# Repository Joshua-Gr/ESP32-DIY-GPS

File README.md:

# ESP32 DIY GPS

A GPS receiver board built around an ESP32-S3 and a u-blox GNSS module, powered from a 12 V vehicle supply.

## Repository layout

| Path | Contents |
|---|---|
| `firmware/` | PlatformIO project (Arduino framework) |
| `hardware/` | KiCad 10 project |
| `hardware/lib/` | Project-local symbols, footprints and 3D models, so the project opens without extra libraries installed |
| `hardware/fab/` | Fabrication outputs, one folder per ordered board revision |

## Hardware

80 × 40 mm, 4-layer PCB.

| Function | Part |
|---|---|
| MCU | Espressif ESP32-S3-WROOM-1-N16R2 (rated −40 to 85 °C ambient) |
| GNSS | u-blox NEO-M9N, external active antenna via U.FL (antenna bias from the receiver's VCC_RF) |
| Power | TI TPS54360 buck regulator, designed for 6–60 V in, 3.3 V / 1.5 A out |
| Input protection | Series Schottky (reverse polarity) and a 33 V TVS on the 12 V input |
| Connectors | 12 V input (Molex Micro-Fit 3.0), USB-C (data only, not powered), 3-pin debug UART header |

The schematic is split into sheets, each laid out in numbered blocks with design and layout notes:

| Sheet | Contents |
|---|---|
| Top level | Block diagram of how the sheets connect |
| Power | Input protection and the 3.3 V buck regulator |
| MCU | ESP32-S3 module, reset and boot buttons, decoupling, I/O series resistors |
| GNSS | NEO-M9N receiver, antenna feed, host UART and test points |
| Connectors | USB-C and the debug UART header |

## Firmware

The ESP32 bridges the GNSS receiver to USB and Bluetooth LE. At boot it sets the
NEO-M9N to 115200 baud and 10 Hz NMEA output (GGA, RMC, VTG, GSA every fix, GSV once
per second); after that every byte from the receiver is forwarded unchanged.

| Interface | Direction | Use |
|---|---|---|
| USB-C (CDC serial) | both | NMEA stream, gpsd, u-center (UBX passes through) |
| BLE Nordic UART Service, advertised as `ESP32-DIY-GPS-XXXX` | TX notify / RX write | NMEA to BLE GNSS apps, UBX commands back to the receiver |
| Debug header (UART0, 115200) | out | Boot and status log |

The board must be powered from the 12 V input; USB-C carries data only. Change the
rate with `-DNAV_RATE_HZ=<n>` in `build_flags`; above 10 Hz, reduce the NMEA sentence
set or switch to UBX output to stay within the serial bandwidth.

```sh
cd firmware
pio run            # build
pio run -t upload  # flash
```

## License

Firmware: GPL-3.0-or-later. Hardware design: CERN-OHL-S-2.0. Third-party
part library: CC-BY-SA-4.0. See [LICENSE.md](LICENSE.md).

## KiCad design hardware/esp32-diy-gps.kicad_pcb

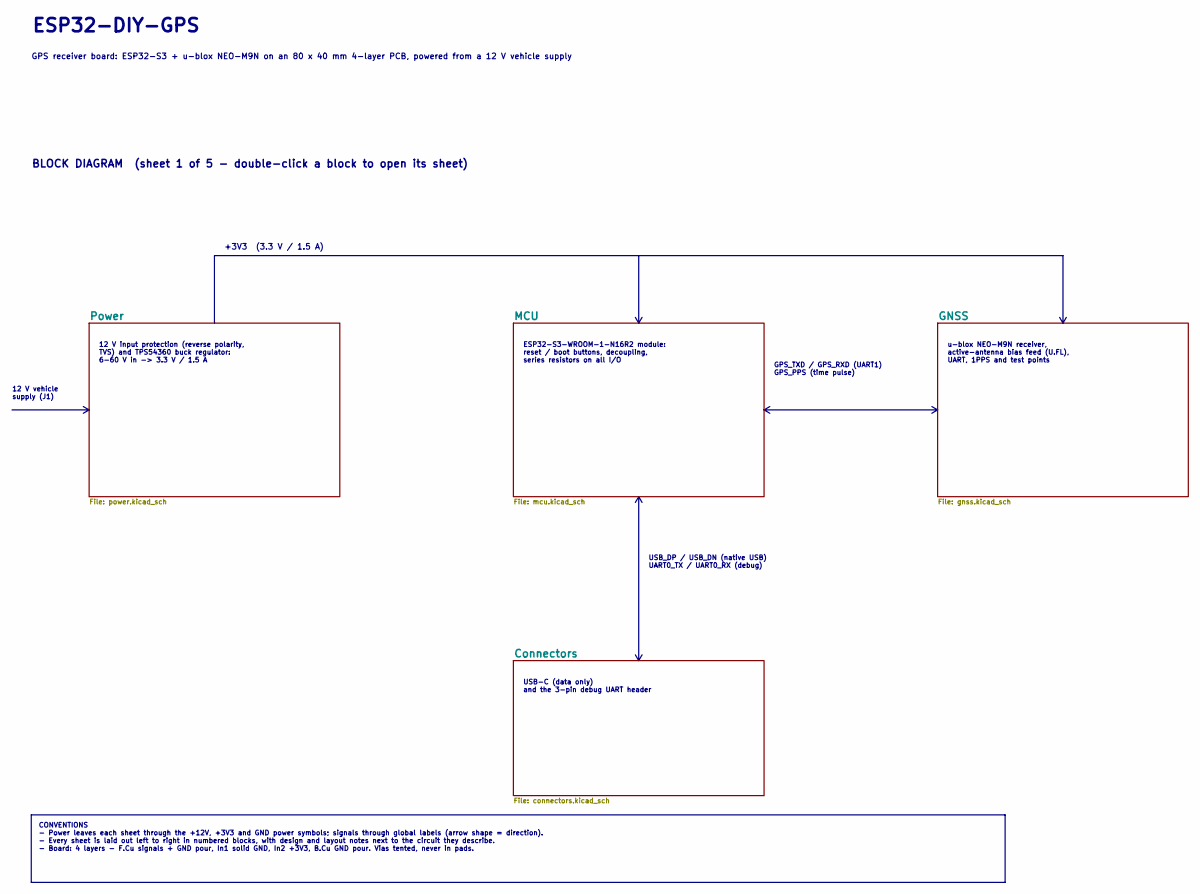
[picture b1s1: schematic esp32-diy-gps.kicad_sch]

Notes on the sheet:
ESP32-DIY-GPS
GPS receiver board: ESP32-S3 + u-blox NEO-M9N on an 80 x 40 mm 4-layer PCB, powered from a 12 V vehicle supply
BLOCK DIAGRAM (sheet 1 of 5 - double-click a block to open its sheet)
12 V input protection (reverse polarity, TVS) and TPS54360 buck regulator: 6-60 V in -> 3.3 V / 1.5 A
ESP32-S3-WROOM-1-N16R2 module: reset / boot buttons, decoupling, series resistors on all I/O
u-blox NEO-M9N receiver, active-antenna bias feed (U.FL), UART, 1PPS and test points
USB-C (data only) and the 3-pin debug UART header
12 V vehicle supply (J1)
+3V3 (3.3 V / 1.5 A)
GPS_TXD / GPS_RXD (UART1) GPS_PPS (time pulse)
USB_DP / USB_DN (native USB) UART0_TX / UART0_RX (debug)
CONVENTIONS - Power leaves each sheet through the +12V, +3V3 and GND power symbols; signals through global labels (arrow shape = direction). - Every sheet is laid out left to right in numbered blocks, with design and layout notes next to the circuit they describe. - Board: 4 layers - F.Cu signals +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

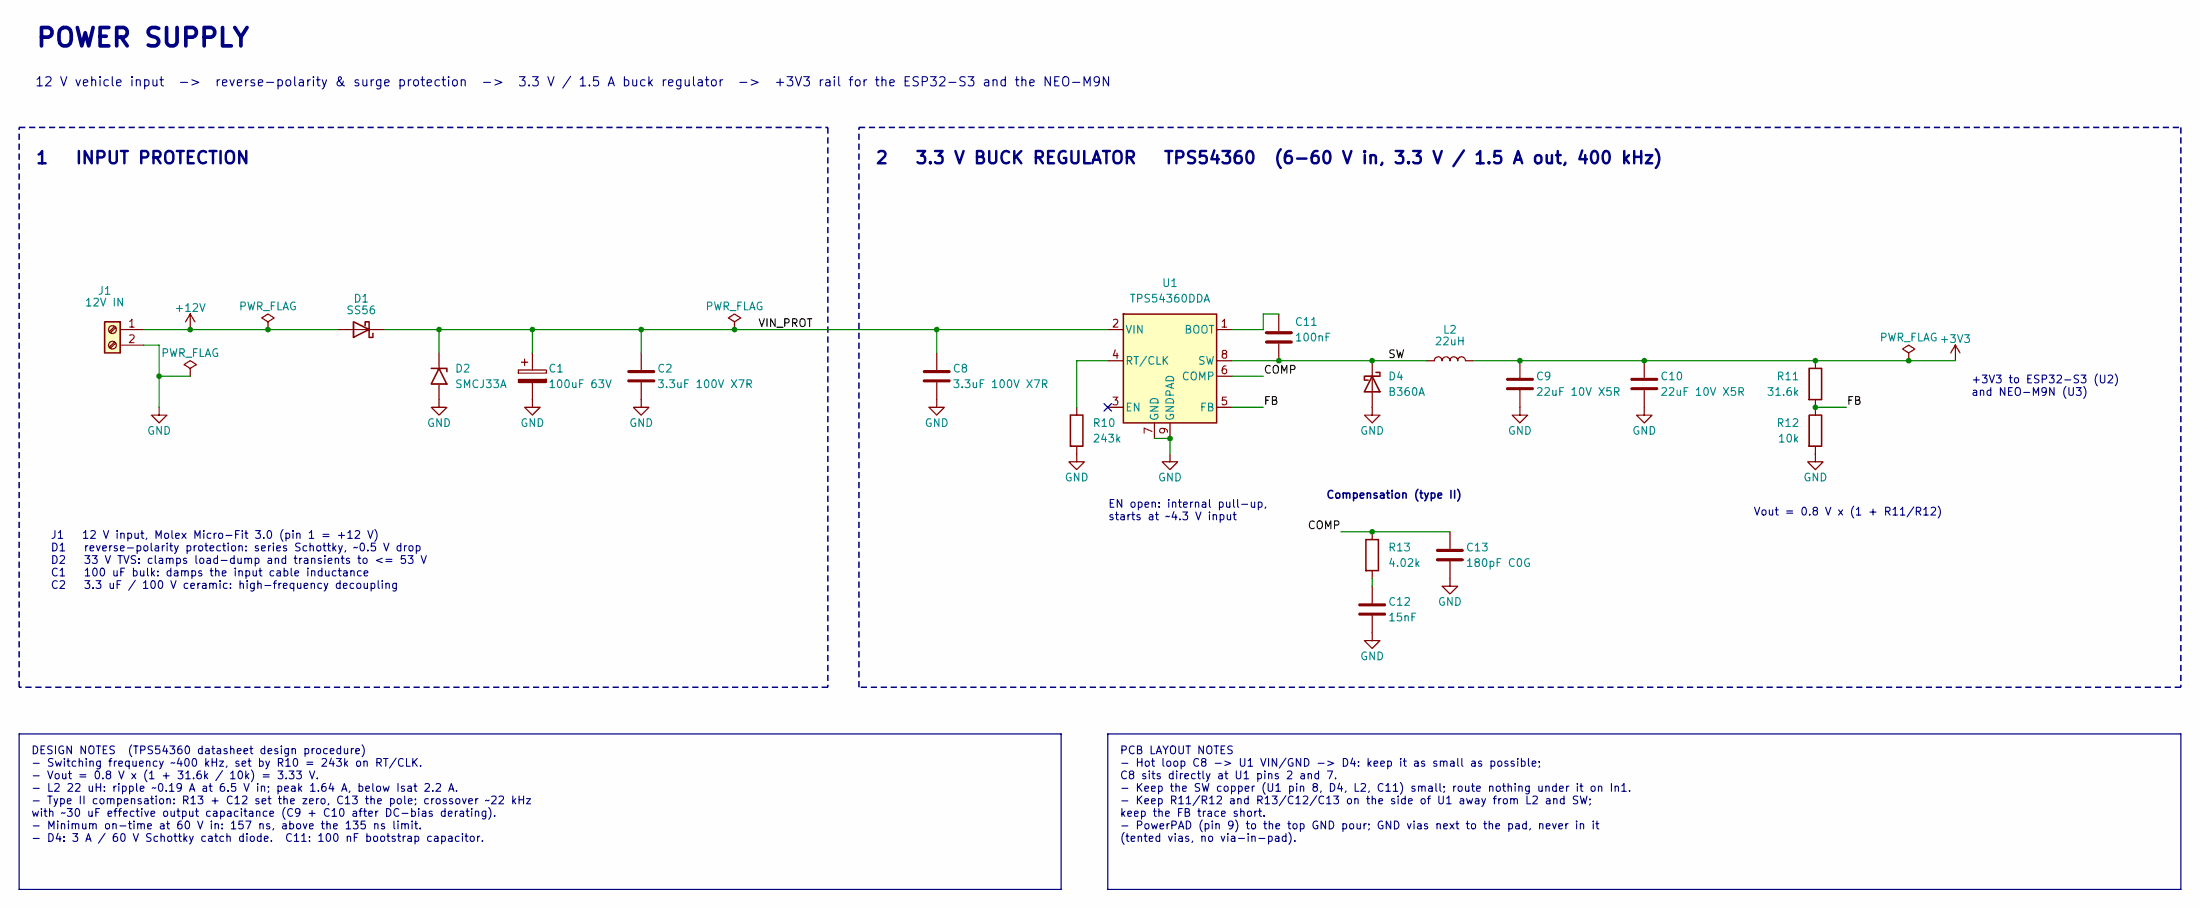
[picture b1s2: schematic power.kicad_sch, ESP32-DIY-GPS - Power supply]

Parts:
C1: 100uF 63V; CP_Elec_10x10; MPN EEE-FK1J101P
C2, C8: 3.3uF 100V X7R; C_1210_3225Metric; MPN FS32X335K101EGG
C9, C10: 22uF 10V X5R; C_0805_2012Metric; MPN CL21A226MPQNNNE
C11: 100nF; C_0805_2012Metric; MPN CL21B104KBCNNNC
C12: 15nF; C_0805_2012Metric; MPN CC0805KRX7R9BB153
C13: 180pF C0G; C_0805_2012Metric; MPN CC0805JRNPO9BN181
D1: SS56; D_SMC; MPN B560C-13-F
D2: SMCJ33A; D_SMC; MPN SMCJ33A
D4: B360A; D_SMA; MPN B360A-13-F
J1: 12V IN; Molex_Micro-Fit_3.0_43650-0212_1x02-1MP_P3.00mm_Horizontal; MPN 43650-0212
L2: 22uH; L_Sunlord_SWPA6045S; MPN SWPA6045S220MT
R10: 243k; R_0805_2012Metric; MPN 0805W8F2433T5E
R11: 31.6k; R_0805_2012Metric; MPN RC0805FR-0731K6L
R12: 10k; R_0805_2012Metric; MPN RC0805FR-0710KL
R13: 4.02k; R_0805_2012Metric; MPN RC0805FR-074K02L
U1: TPS54360DDA; TI_SO-PowerPAD-8; MPN TPS54360DDAR

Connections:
+3V3: C9.1, C10.1, L2.2, R11.1; also elsewhere on the board
+12V: D1.2 (A), J1.1
/Power/COMP: C13.1, R13.1, U1.6 (COMP)
/Power/FB: R11.2, R12.1, U1.5 (FB)
/Power/SW: C11.2, D4.1 (K), L2.1, U1.8 (SW)
/Power/VIN_PROT: C1.1, C2.1, C8.1, D1.1 (K), D2.1 (A1), U1.2 (VIN)
GND: C1.2, C2.2, C8.2, C9.2, C10.2, C12.2, C13.2, D2.2 (A2), D4.2 (A), J1.2, R10.2, R12.2, U1.7 (GND), U1.9 (GNDPAD); also elsewhere on the board
unnamed: C12.1, R13.2
unnamed: C11.1, U1.1 (BOOT)
unnamed: R10.1, U1.4 (RT/CLK)

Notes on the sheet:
EN open: internal pull-up, starts at ~4.3 V input
Compensation (type II)
12 V vehicle input -> reverse-polarity & surge protection -> 3.3 V / 1.5 A buck regulator -> +3V3 rail for the ESP32-S3 and the NEO-M9N
2 3.3 V BUCK REGULATOR TPS54360 (6-60 V in, 3.3 V / 1.5 A out, 400 kHz)
1 INPUT PROTECTION
J1 12 V input, Molex Micro-Fit 3.0 (pin 1 = +12 V) D1 reverse-polarity protection: series Schottky, ~0.5 V drop D2 33 V TVS: clamps load-dump and transients to <= 53 V C1 100 uF bulk: damps the input cable inductance C2 3.3 uF / 100 V ceramic: high-frequency decoupling
+3V3 to ESP32-S3 (U2) and NEO-M9N (U3)
POWER SUPPLY
Vout = 0.8 V x (1 + R11/R12)
PCB LAYOUT NOTES - Hot loop C8 -> U1 VIN/GND -> D4: keep it as small as possible; C8 sits directly at U1 pins 2 and 7. - Keep the SW copper (U1 pin 8, D4, L2, C11) small; route nothing under it on In1. - Keep R11/R12 and R13/C12/C13 on the side of U1 away from L2 and SW; keep the FB trace short. - 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
DESIGN NOTES (TPS54360 datasheet design procedure) - Switching frequency ~400 kHz, set by R10 = 243k on RT/CLK. - Vout = 0.8 V x (1 + 31.6k / 10k) = 3.33 V. - L2 22 uH: ripple ~0.19 A at 6.5 V in; peak 1.64 A, below Isat 2.2 A. - Type II compensation: R13 + C12 set the zero, C13 the pole; crossover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

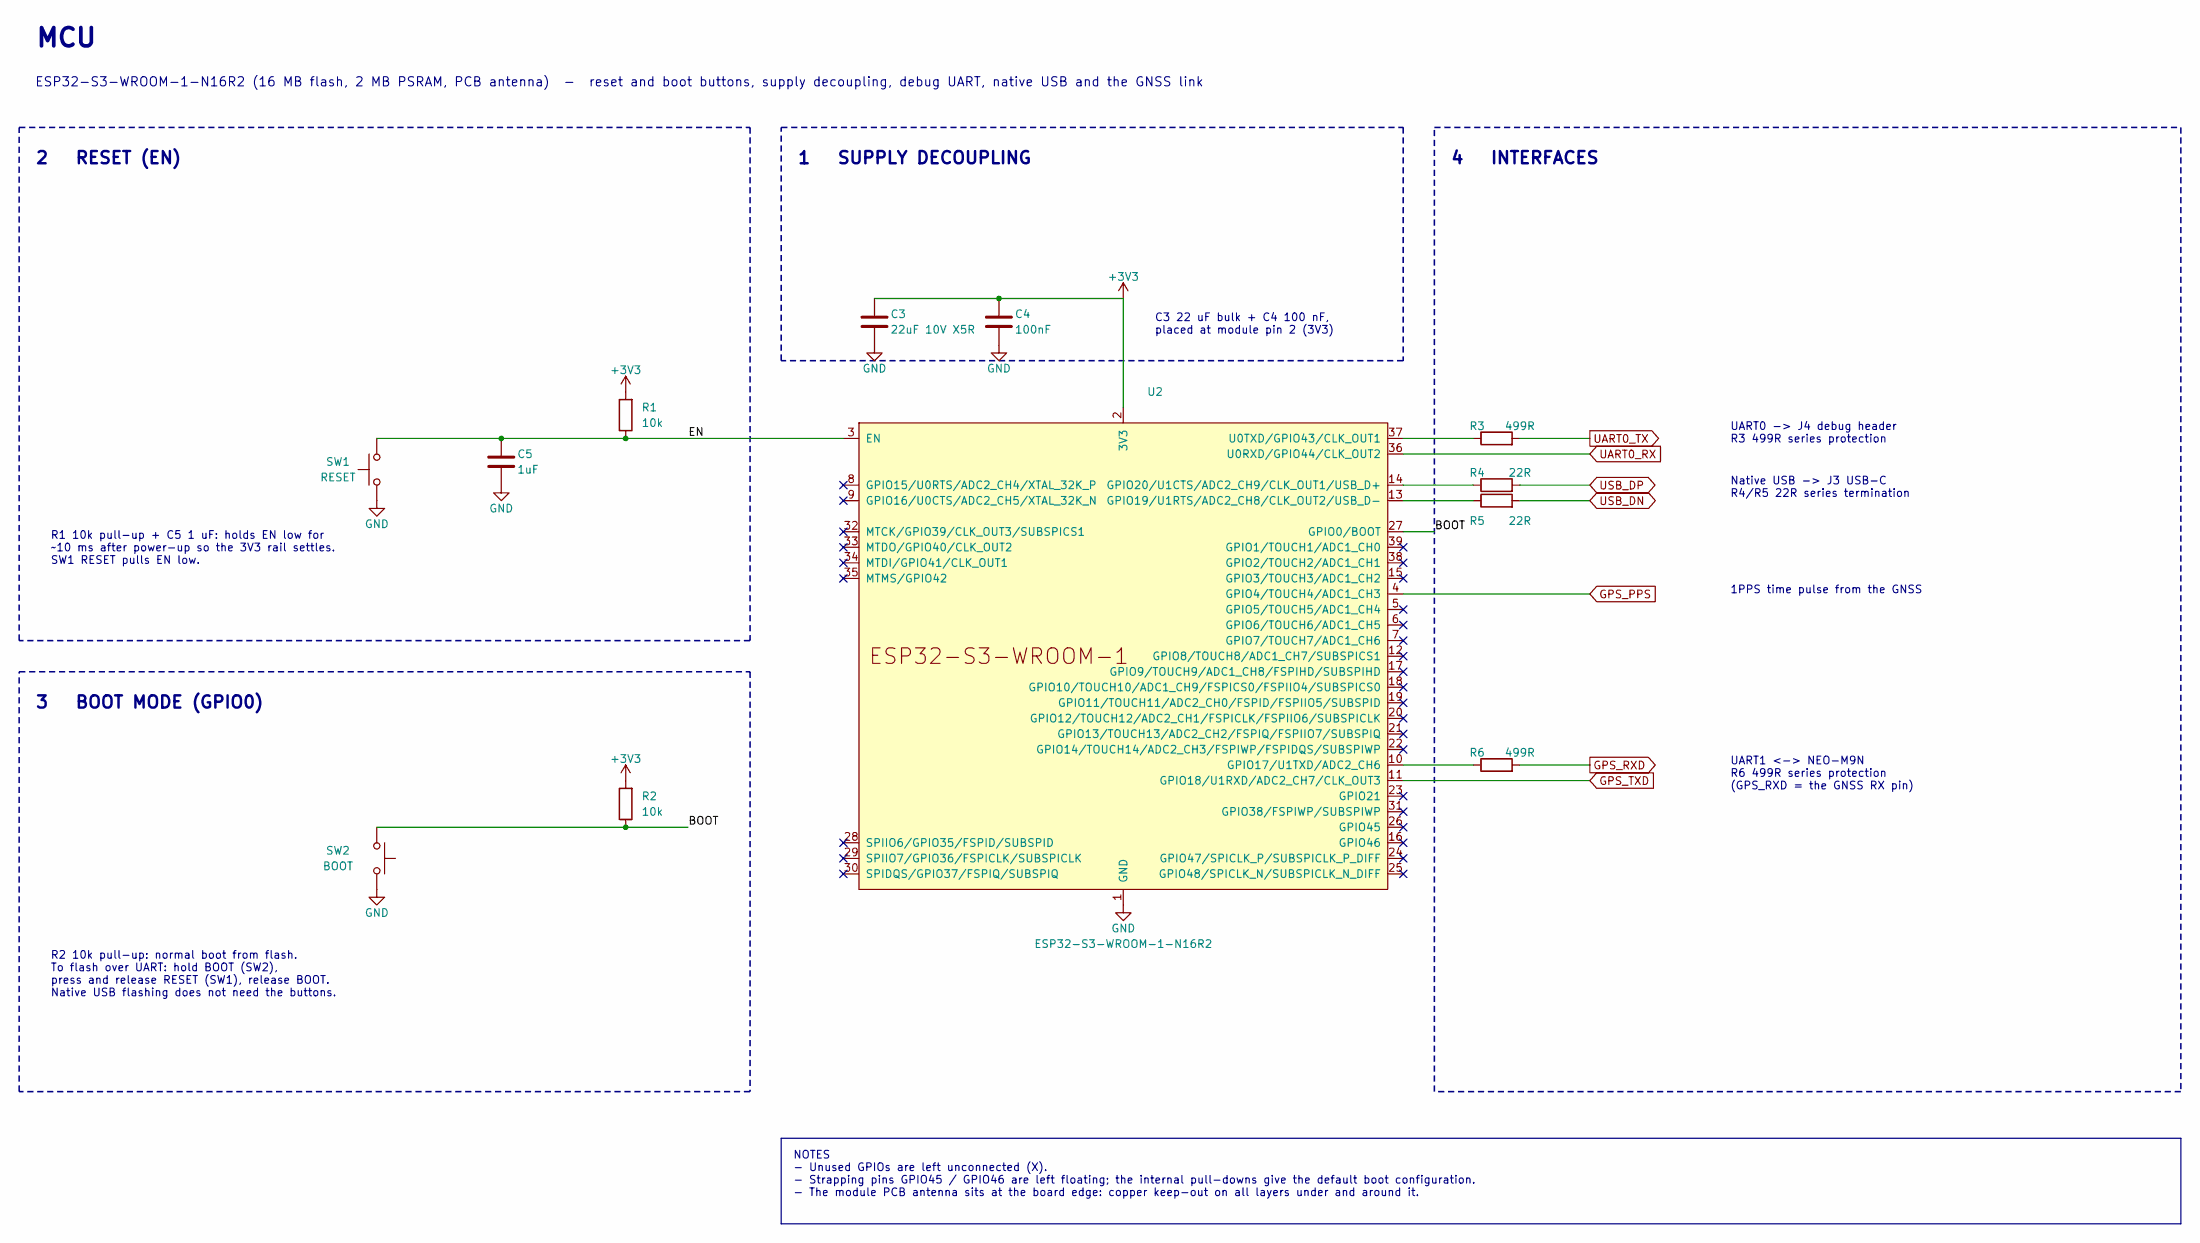
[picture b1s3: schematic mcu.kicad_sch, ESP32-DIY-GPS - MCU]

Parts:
C3: 22uF 10V X5R; C_0805_2012Metric; MPN CL21A226MPQNNNE
C4: 100nF; C_0805_2012Metric; MPN CL21B104KBCNNNC
C5: 1uF; C_0805_2012Metric; MPN CL21B105KOFNNNE
R1, R2: 10k; R_0805_2012Metric; MPN RC0805FR-0710KL
R3, R6: 499R; R_0805_2012Metric; MPN RC0805FR-07499RL
R4, R5: 22R; R_0805_2012Metric; MPN RC0805FR-0722RL
SW1: RESET; SW_Push_1P1T_XKB_TS-1187A; MPN TS-1187A-B-A-B
SW2: BOOT; SW_Push_1P1T_XKB_TS-1187A; MPN TS-1187A-B-A-B
U2: ESP32-S3-WROOM-1-N16R2; ESP32-S3-WROOM-1; MPN ESP32-S3-WROOM-1-N16R2

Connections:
+3V3: C3.2, C4.2, R1.2, R2.2, U2.2 (3V3); also elsewhere on the board
/MCU/BOOT: R2.1, SW2.1, U2.27 (GPIO0/BOOT)
/MCU/EN: C5.1, R1.1, SW1.2, U2.3 (EN)
GND: C3.1, C4.1, C5.2, SW1.1, SW2.2, U2.1 (GND), U2.40 (GND), U2.41 (GND); also elsewhere on the board
GPS_PPS: U2.4 (GPIO4/TOUCH4/ADC1_CH3); also elsewhere on the board
GPS_RXD: R6.2; also elsewhere on the board
GPS_TXD: U2.11 (GPIO18/U1RXD/ADC2_CH7/CLK_OUT3); also elsewhere on the board
unnamed: R6.1, U2.10 (GPIO17/U1TXD/ADC2_CH6)
unnamed: R5.1, U2.13 (GPIO19/U1RTS/ADC2_CH8/CLK_OUT2/USB_D-)
unnamed: R4.1, U2.14 (GPIO20/U1CTS/ADC2_CH9/CLK_OUT1/USB_D+)
unnamed: R3.1, U2.37 (U0TXD/GPIO43/CLK_OUT1)
UART0_RX: U2.36 (U0RXD/GPIO44/CLK_OUT2); also elsewhere on the board
UART0_TX: R3.2; also elsewhere on the board
USB_DN: R5.2; also elsewhere on the board
USB_DP: R4.2; also elsewhere on the board

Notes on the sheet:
MCU
ESP32-S3-WROOM-1-N16R2 (16 MB flash, 2 MB PSRAM, PCB antenna) - reset and boot buttons, supply decoupling, debug UART, native USB and the GNSS link
1 SUPPLY DECOUPLING
C3 22 uF bulk + C4 100 nF, placed at module pin 2 (3V3)
2 RESET (EN)
R1 10k pull-up + C5 1 uF: holds EN low for ~10 ms after power-up so the 3V3 rail settles. SW1 RESET pulls EN low.
3 BOOT MODE (GPIO0)
R2 10k pull-up: normal boot from flash. To flash over UART: hold BOOT (SW2), press and release RESET (SW1), release BOOT. Native USB flashing does not need the buttons.
4 INTERFACES
UART0 -> J4 debug header R3 499R series protection
Native USB -> J3 USB-C R4/R5 22R series termination
1PPS time pulse from the GNSS
UART1 <-> NEO-M9N R6 499R series protection (GPS_RXD = the GNSS RX pin)
NOTES - Unused GPIOs are left unconnected (X). - Strapping pins GPIO45 / GPIO46 are left floating; the internal pull-downs give the default boot configuration. - The module PCB antenna sits at the board edge: copper keep-out on all layers under and around it.

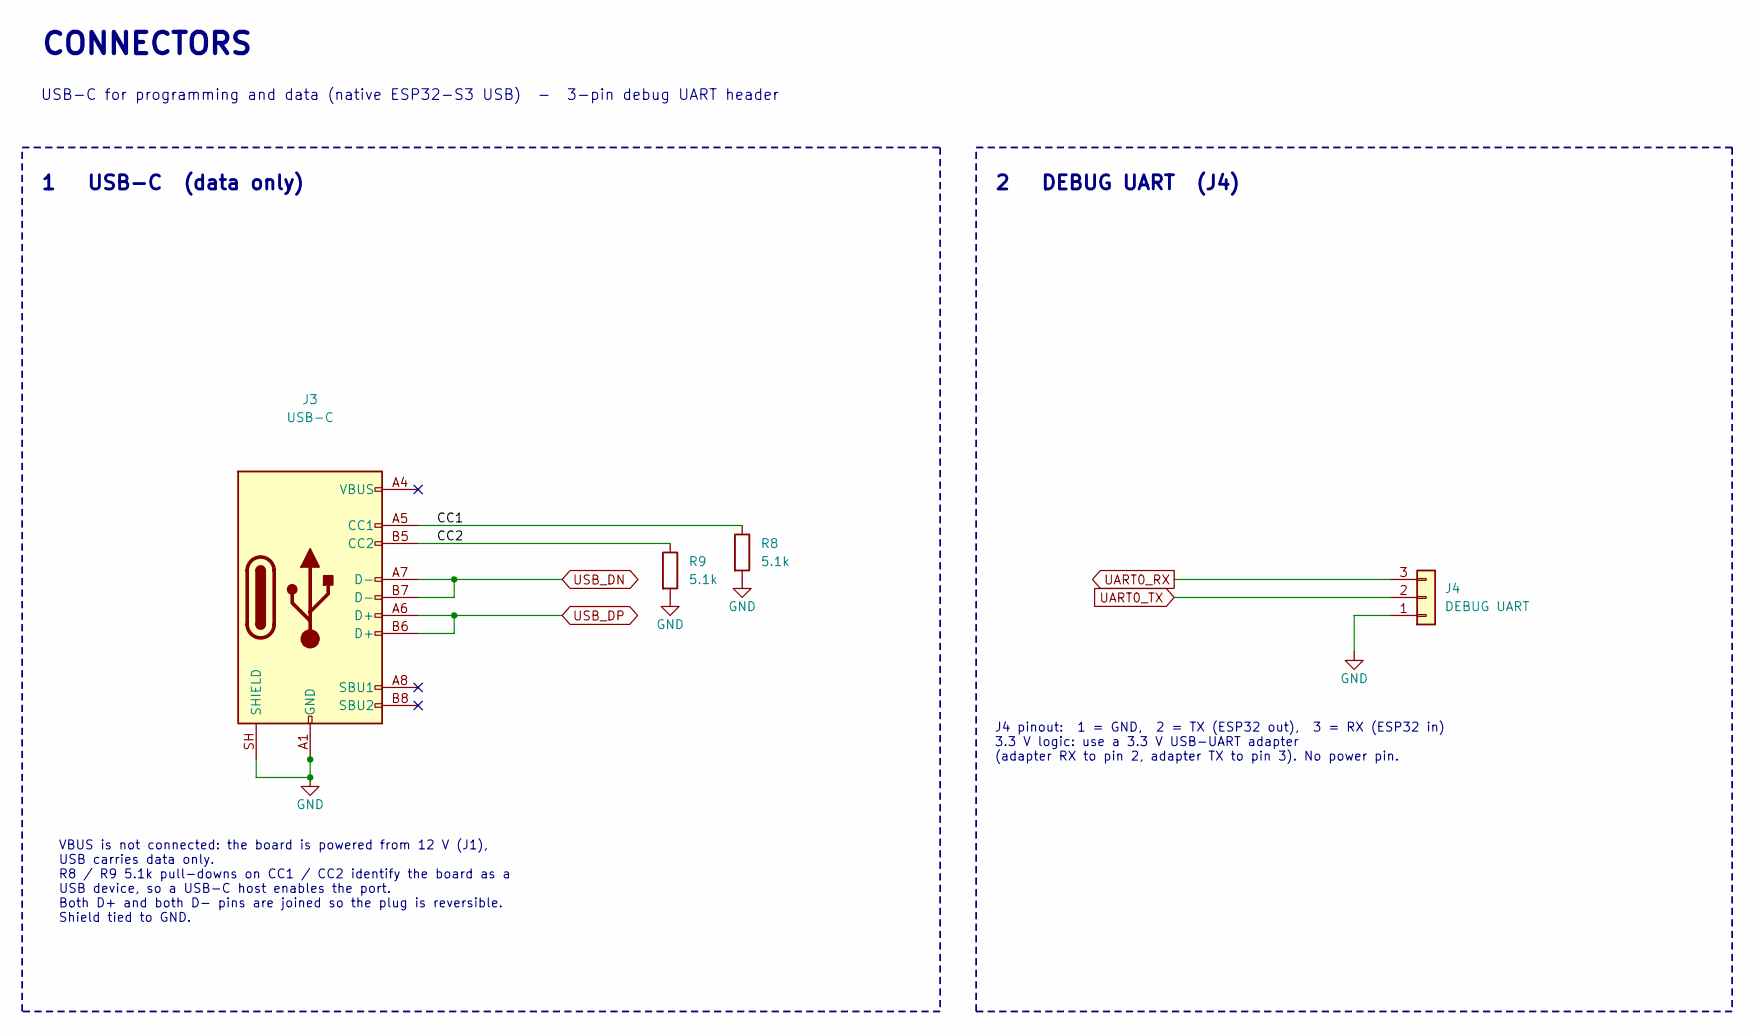
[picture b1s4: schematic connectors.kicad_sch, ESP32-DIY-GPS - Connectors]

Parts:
J3: USB-C; USB_C_Receptacle_GCT_USB4110; MPN USB4110-GF-A
J4: DEBUG UART; PinHeader_1x03_P2.54mm_Vertical_SMD_Pin1Right; MPN M20-8770342
R8, R9: 5.1k; R_0805_2012Metric; MPN RC0805FR-075K1L

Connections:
/Connectors/CC1: J3.A5 (CC1), R8.1
/Connectors/CC2: J3.B5 (CC2), R9.1
GND: J3.A1 (GND), J3.A12 (GND), J3.B1 (GND), J3.B12 (GND), J3.SH (SHIELD), J4.1, R8.2, R9.2; also elsewhere on the board
UART0_RX: J4.3; also elsewhere on the board
UART0_TX: J4.2; also elsewhere on the board
USB_DN: J3.A7 (D-), J3.B7 (D-); also elsewhere on the board
USB_DP: J3.A6 (D+), J3.B6 (D+); also elsewhere on the board

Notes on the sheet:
CONNECTORS
USB-C for programming and data (native ESP32-S3 USB) - 3-pin debug UART header
1 USB-C (data only)
VBUS is not connected: the board is powered from 12 V (J1), USB carries data only. R8 / R9 5.1k pull-downs on CC1 / CC2 identify the board as a USB device, so a USB-C host enables the port. Both D+ and both D- pins are joined so the plug is reversible. Shield tied to GND.
2 DEBUG UART (J4)
J4 pinout: 1 = GND, 2 = TX (ESP32 out), 3 = RX (ESP32 in) 3.3 V logic: use a 3.3 V USB-UART adapter (adapter RX to pin 2, adapter TX to pin 3). No power pin.

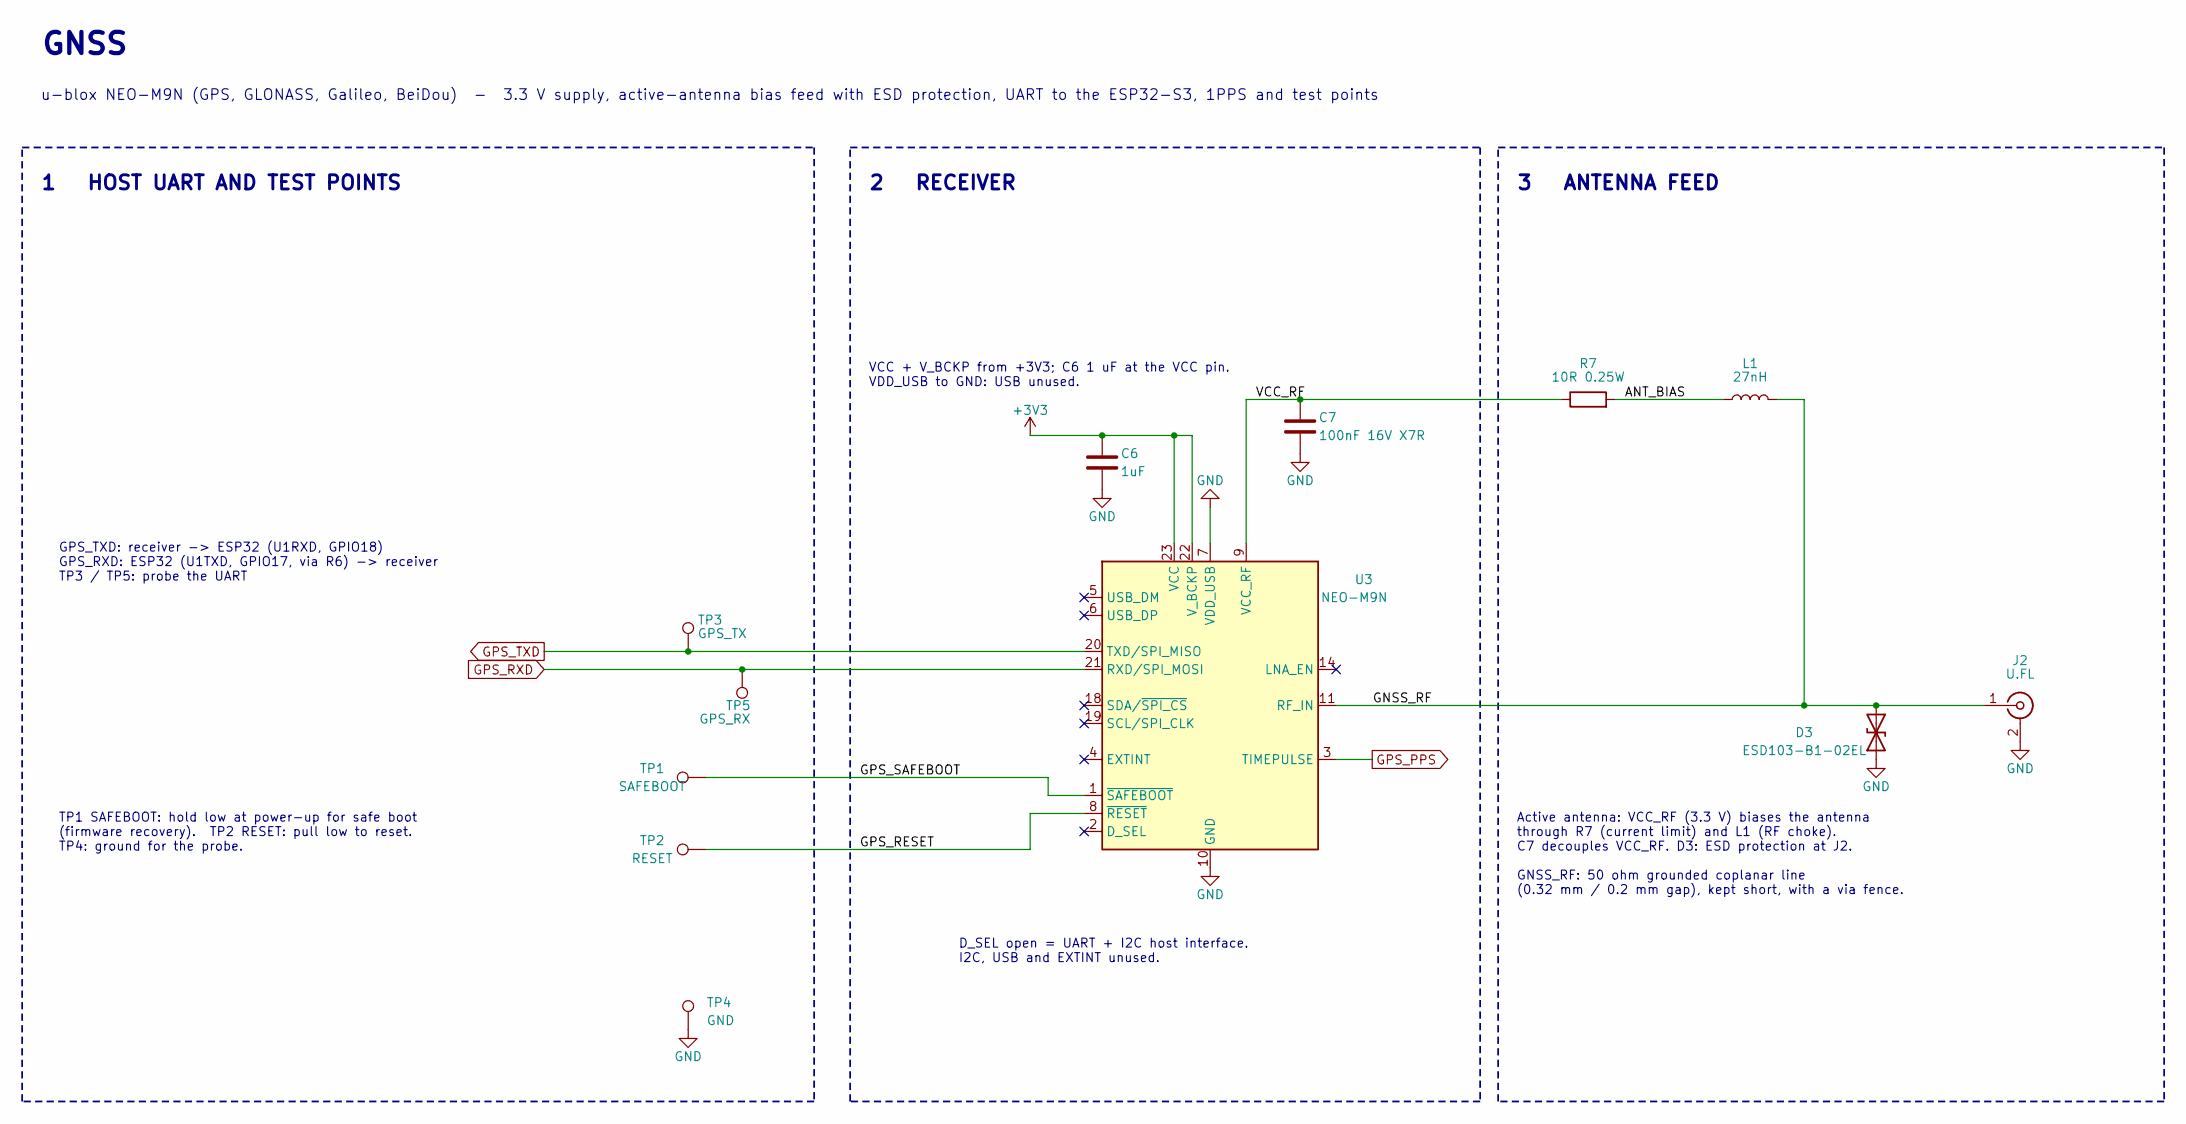
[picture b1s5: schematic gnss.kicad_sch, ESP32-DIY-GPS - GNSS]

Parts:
C6: 1uF; C_0805_2012Metric; MPN CL21B105KOFNNNE
C7: 100nF 16V X7R; C_0805_2012Metric; MPN CL21B104KBCNNNC
D3: ESD103-B1-02EL; Infineon_TSLP-2-20; MPN ESD103B102ELE6327XTMA1
J2: U.FL; U.FL_Hirose_U.FL-R-SMT-1_Vertical; MPN U.FL-R-SMT-1(80)
L1: 27nH; L_0402_1005Metric; MPN LQG15HS27NJ02D
R7: 10R 0.25W; R_1206_3216Metric; MPN RC1206FR-0710RL
TP1: SAFEBOOT; TestPoint_Pad_D1.5mm
TP2: RESET; TestPoint_Pad_D1.5mm
TP3: GPS_TX; TestPoint_Pad_D1.5mm
TP4: GND; TestPoint_Pad_D1.5mm
TP5: GPS_RX; TestPoint_Pad_D1.5mm
U3: NEO-M9N; ublox_NEO; MPN NEO-M9N-00B

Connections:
+3V3: C6.2, U3.22 (V_BCKP), U3.23 (VCC); also elsewhere on the board
/GNSS/ANT_BIAS: L1.1, R7.2
/GNSS/GNSS_RF: D3.2 (A2), J2.1 (In), L1.2, U3.11 (RF_IN)
/GNSS/GPS_RESET: TP2.1 (1_1), U3.8 (~RESET)
/GNSS/GPS_SAFEBOOT: TP1.1 (1_1), U3.1 (~SAFEBOOT)
/GNSS/VCC_RF: C7.1, R7.1, U3.9 (VCC_RF)
GND: C6.1, C7.2, D3.1 (A1), J2.2 (Ext), TP4.1 (1_1), U3.7 (VDD_USB), U3.10 (GND), U3.12 (GND), U3.13 (GND), U3.24 (GND); also elsewhere on the board
GPS_PPS: U3.3 (TIMEPULSE); also elsewhere on the board
GPS_RXD: TP5.1 (1_1), U3.21 (RXD/SPI_MOSI); also elsewhere on the board
GPS_TXD: TP3.1 (1_1), U3.20 (TXD/SPI_MISO); also elsewhere on the board

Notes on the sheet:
GNSS
u-blox NEO-M9N (GPS, GLONASS, Galileo, BeiDou) - 3.3 V supply, active-antenna bias feed with ESD protection, UART to the ESP32-S3, 1PPS and test points
2 RECEIVER
VCC + V_BCKP from +3V3; C6 1 uF at the VCC pin. VDD_USB to GND: USB unused.
D_SEL open = UART + I2C host interface. I2C, USB and EXTINT unused.
3 ANTENNA FEED
Active antenna: VCC_RF (3.3 V) biases the antenna through R7 (current limit) and L1 (RF choke). C7 decouples VCC_RF. D3: ESD protection at J2. GNSS_RF: 50 ohm grounded coplanar line (0.32 mm / 0.2 mm gap), kept short, with a via fence.
1 HOST UART AND TEST POINTS
GPS_TXD: receiver -> ESP32 (U1RXD, GPIO18) GPS_RXD: ESP32 (U1TXD, GPIO17, via R6) -> receiver TP3 / TP5: probe the UART
TP1 SAFEBOOT: hold low at power-up for safe boot (firmware recovery). TP2 RESET: pull low to reset. TP4: ground for the probe.

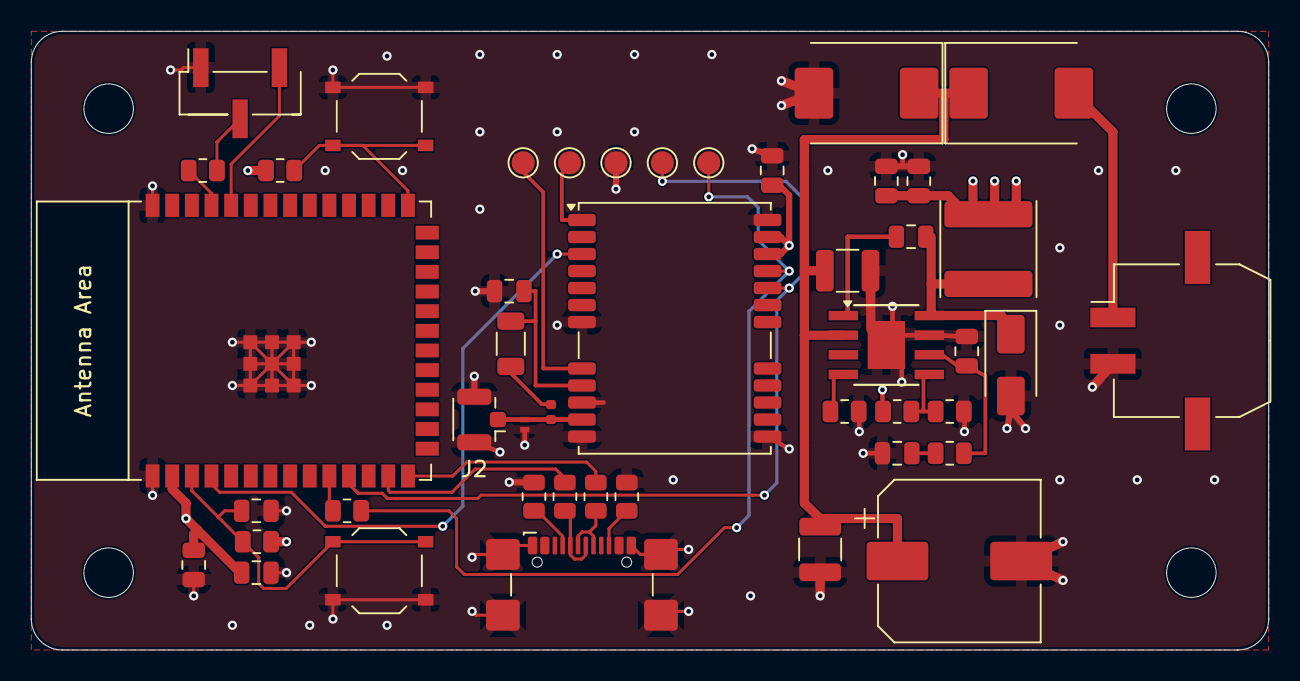
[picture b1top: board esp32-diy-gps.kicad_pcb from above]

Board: 4 copper layers, 80.0 x 40.0 mm, 50 parts (0 on the bottom side), 30 nets.

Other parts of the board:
H1, H2, H3, H4: MountingHole_3.2mm_M3
